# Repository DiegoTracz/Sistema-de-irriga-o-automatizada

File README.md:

# Sistema de irrigacao automatizada
# Interruptor inteligente customizável
O projeto irrigação automatizada, é uma solução IoT baseada no ESP8266 com o objetivo criar um sistema de irrigação automatico de baixo custo.
  <li> Passo a passo montagem: https://www.youtube.com/watch?v=MeowtO0F4BM&ab_channel=BlumenMaker</li>

<h2><b>Bibliotecas necessárias</b></h2>

|  <b>Nome</b> |  <b>Link</b> |
|---|---|
| ArduinoJson  |<a href="https://github.com/bblanchon/ArduinoJson/">GIT</a>  |     
|  WebSockets | <a href="https://github.com/Links2004/arduinoWebSockets/">GIT</a>  |  
| Sirincpro  |  <a href="https://github.com/sinricpro/esp8266-esp32-sdk/">GIT</a> |   
| WifiManager  |<a href="https://github.com/tzapu/WiFiManager/">GIT</a> |   

<h2><b>Hardware</b></h2>

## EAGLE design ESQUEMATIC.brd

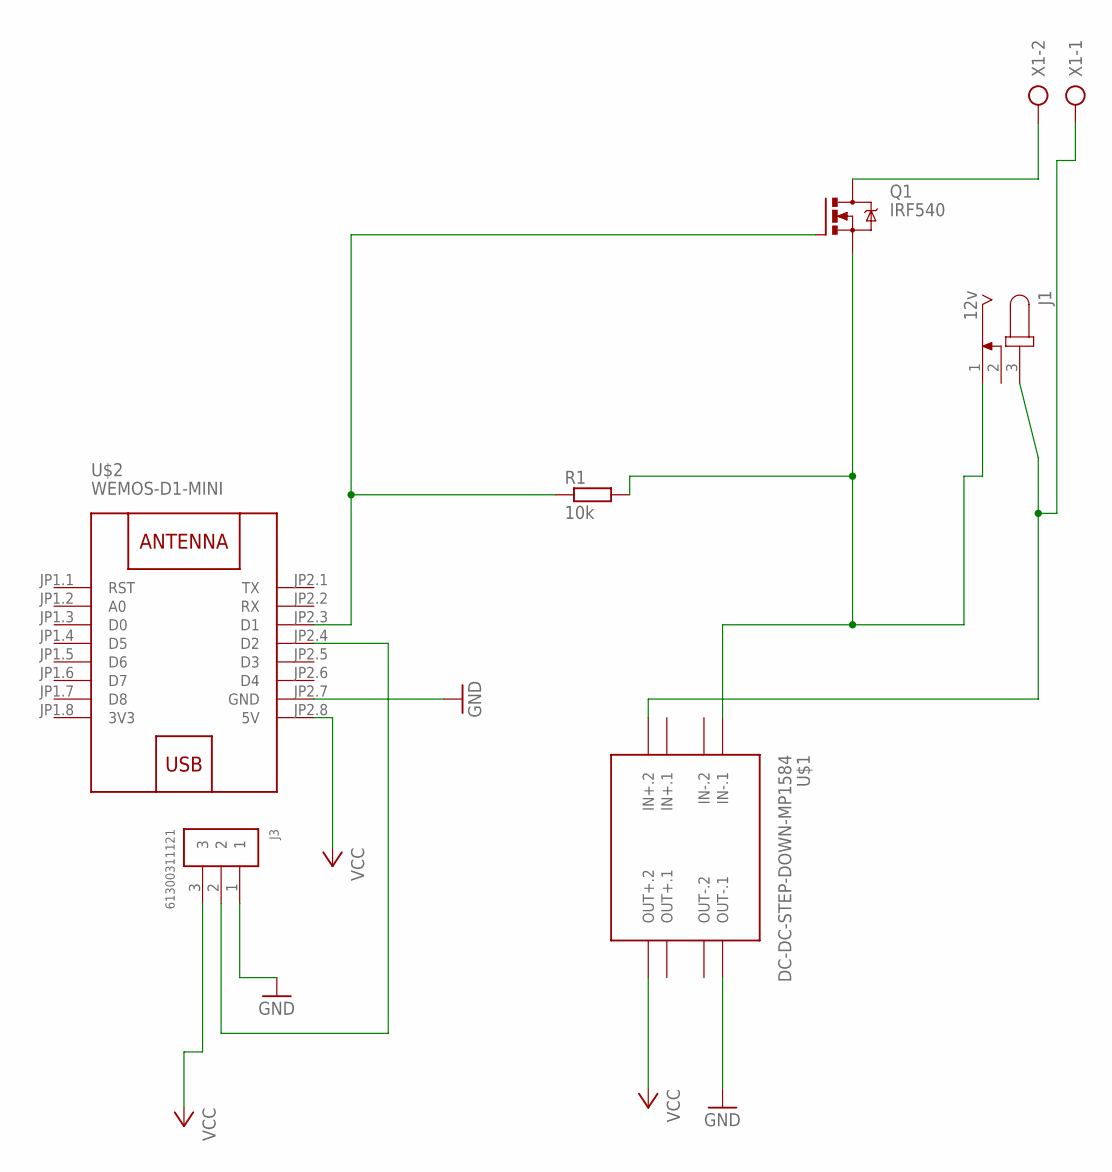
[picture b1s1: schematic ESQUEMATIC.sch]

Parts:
J1: 12v; SPC4077
J3: 61300311121
Q1: IRF540; TO220BV
R1: 10k; 0204/7
U$1: DC-DC-STEP-DOWN-MP1584
U$2: WEMOS-D1-MINI
X1: AK300/2

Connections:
3V3: U$2.JP1.8 (3V3)
GND: J3.1, U$1.OUT-.1, U$2.JP2.7 (GND)
unnamed: J1.3, U$1.IN+.2, X1.1
unnamed: J1.1, Q1.S, R1.2, U$1.IN-.1
unnamed: Q1.D, X1.2
unnamed: Q1.G, R1.1, U$2.JP2.3 (D1)
unnamed: J3.2, U$2.JP2.4 (D2)
VCC: J3.3, U$1.OUT+.2, U$2.JP2.8 (5V)

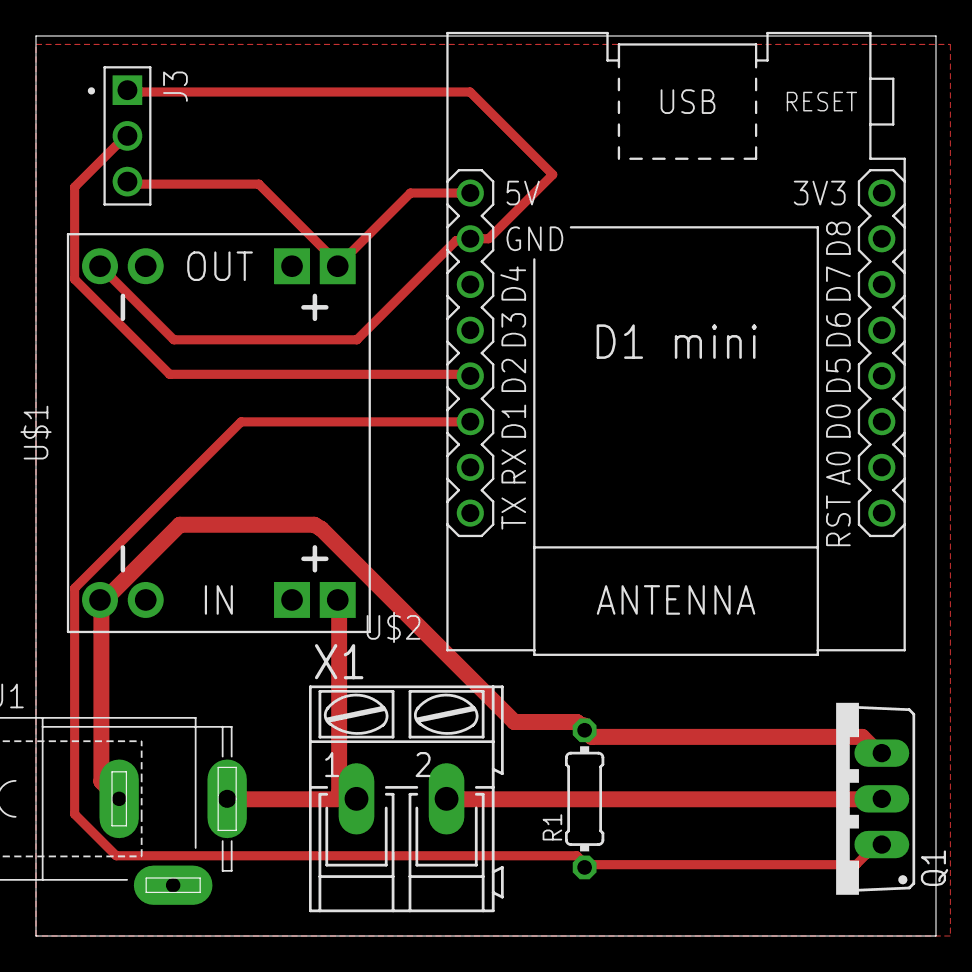
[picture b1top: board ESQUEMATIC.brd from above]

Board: 2 copper layers, 50.0 x 50.0 mm, 7 parts (0 on the bottom side), 7 nets.

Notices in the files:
parts and their libraries:
estpdown: Released under the Creative Commons Attribution 4.0 International License: http://creativecommons.org/licenses/by/4.0
